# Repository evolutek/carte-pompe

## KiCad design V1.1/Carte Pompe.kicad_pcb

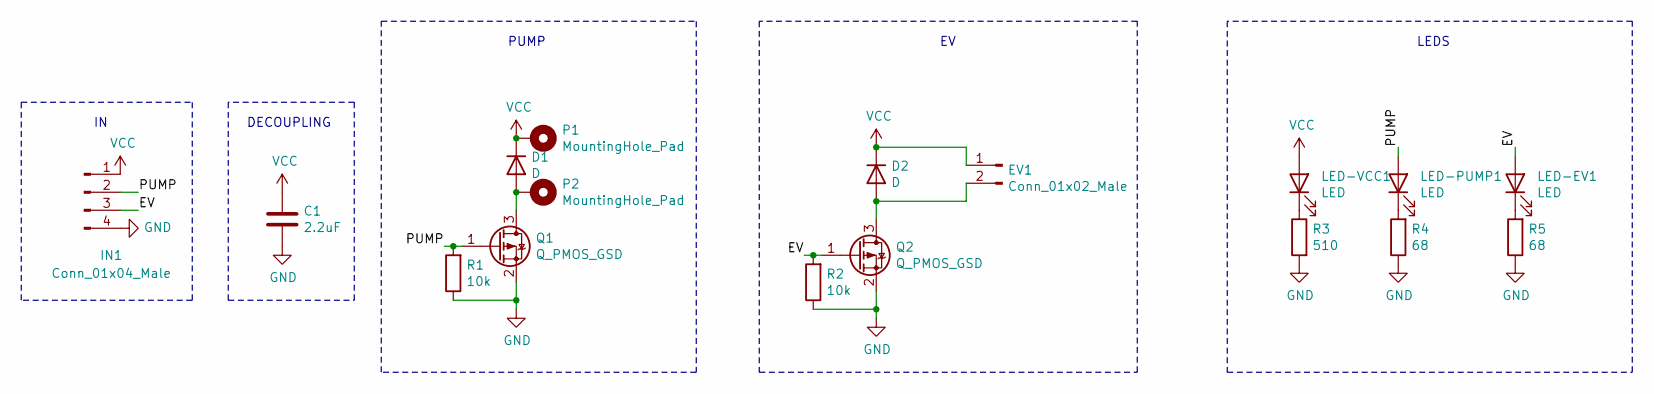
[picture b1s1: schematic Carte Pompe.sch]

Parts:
C1: 2.2uF; C_0603_1608Metric
D1, D2: D; D_SMB
EV1: Conn_01x02_Male; B02B-PASK
IN1: Conn_01x04_Male; B04B-PASK
LED-EV1: LED; LED_0805_2012Metric
LED-PUMP1: LED; LED_0805_2012Metric
LED-VCC1: LED; LED_0805_2012Metric
P1, P2: MountingHole_Pad; MountingHole_2.5mm_Pad
Q1, Q2: Q_PMOS_GSD; SOT-23
R1, R2: 10k; R_0603_1608Metric
R3: 510; R_0603_1608Metric
R4, R5: 68; R_0603_1608Metric

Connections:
/EV: IN1.3, LED-EV1.2 (A), Q2.1 (G), R2.2
/PUMP: IN1.2, LED-PUMP1.2 (A), Q1.1 (G), R1.2
GND: C1.2, IN1.4, Q1.2 (S), Q2.2 (S), R1.1, R2.1, R3.2, R4.1, R5.1
unnamed: D1.2 (A), P2.1, Q1.3 (D)
unnamed: D2.2 (A), EV1.2, Q2.3 (D)
unnamed: LED-EV1.1 (K), R5.2
unnamed: LED-PUMP1.1 (K), R4.2
unnamed: LED-VCC1.1 (K), R3.1
VCC: C1.1, D1.1 (K), D2.1 (K), EV1.1, IN1.1, LED-VCC1.2 (A), P1.1

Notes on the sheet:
PUMP
LEDS
DECOUPLING

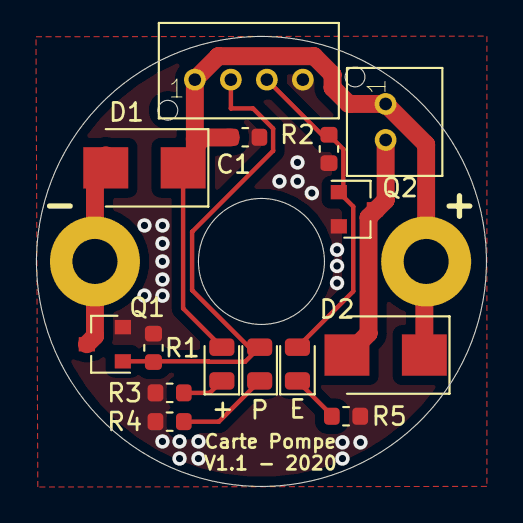
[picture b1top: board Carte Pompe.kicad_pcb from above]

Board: 2 copper layers, 25.0 x 25.0 mm, 17 parts (0 on the bottom side), 9 nets.

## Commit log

2019-12-14 Add a gitignore
2019-12-15 [V1] Add Lib
2019-12-15 [V1] First Version, need to check before production
2020-01-24 [V1.0] Release
2020-06-12 Add V1.1
